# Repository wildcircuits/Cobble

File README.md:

# Cobble 

Cobble is a development board designed to give easy access to sound, environment, and input while being easy to program with CircuitPython.

## Features

- ESP32-S3 Supermini module
- Vibration Sensor
- Light Sensor
- RGB LED
- Speaker
- Button
- Grove Connector
- Stemma Connector
- Battery Connector
- Power Switch 
- IO Header

## Board revisions

| Revision | Status | Notes |
| --- | --- | --- |
| **Rev 2** | **Current - first production run** | Fixed the Stemma connector, which was wired backwards on Rev 1 (the main change). Silkscreen updated, including a QR code. R3 (light sensor divider resistor) set to 10k - it worked at 1M as well, but 10k matches the other 10k resistor and reduces unique part count. Gerbers are in `Cobble-board/fab`. |
| **Rev 1** | Design Validation | 2 layer board test with all features implemented.  Fabricated 3 boards at OSHPark. Established the current pin map (below). |
| **Rev 0** | Concept Validation | Single-layer test board with seperate schematic and layout in `Cobble-board-test/` |

Pins did not change between Rev 1 and Rev 2, so the pin map below applies to both.

## ESP32S3-supermini Pinout

Link: https://www.espboards.dev/esp32/esp32-s3-super-mini/

## Pin mapping 

| ESP32-S3-super-mini Pin | Function | Notes | CircuitPython |
| --- | --- | --- | --- |
| GPIO7 | Light Sensor | Analog read with `analogio.AnalogIn`. GPIO7 is analog-capable, so it maps to A6. | `board.A6` |
| GPIO35 | PushButton | Configure as input with pull up. PushButton is active low. | `board.IO35` |
| GPIO9 | Vibration Sensor | Configure as input with pull up. Vibration is active low. | `board.IO9` |
| GPIO8 | Buzzer | **Never leave high!** Set as output low when not in use. Drive with PWM 50% duty cycle to create sound. | `board.IO8` |
| GPIO48 | NeoPixel | RGB status LED. | `board.IO48` |
| GPIO16 | SCL | I2C for the J3 Stemma and J4 Grove connectors. 4k7 pull-up pads on the board (R4-R7) are do-not-place, so pull-ups come from the attached device. | `board.IO16` |
| GPIO17 | SDA | I2C for the J3 Stemma and J4 Grove connectors. 4k7 pull-up pads on the board (R4-R7) are do-not-place, so pull-ups come from the attached device. | `board.IO17` |
| GPIO1, GPIO2, GPIO4, GPIO5, GPIO6, GPIO15 | Header GPIOs | General-purpose header pins aligned with power and ground pairs. | `board.IOx` |
| GPIO10, GPIO11, GPIO12, GPIO13 | Header GPIOs (SPI) | Header pins aligned for SPI (native SPI pins). | `board.IOx` |

Reference example code using the full Rev 1 pin map: `CircuitPython/Cobble-Rev1/test/code.py`.

## Design notes

Note about 5V Power:
- When USB is connected this will be 5V from VBUS
- When running from a battery this will be Vbatt-V_protection_diode
- Battery can only charge when USB is connected and power switch is 'ON'

## CircuitPython Notes

Testing completed with: 
- Version: 10.3.1
- Using the ESP32-S3-Zero build of CircuitPython.  It is a good standin for the super mini on our board: https://circuitpython.org/board/waveshare_esp32_s3_zero/
- the `boot_out.txt` file is an informational text file automatically generated on the root of the CIRCUITPY drive every time a CircuitPython board powers up or resets.  Contains:
  - CircuitPython Version
  - Build Date
  - Board Model
  - Board ID
  - UID
  - MAC

### Tips & tricks
- **Pin objects**: 
  - Digital pins are `board.IOx` (e.g. `board.IO35` for the pushbutton)
  - The analog light sensor is `board.A6` (GPIO7).
- **Analog input**: 
  - Use `analogio.AnalogIn(pin)`. There is no `board.ADC()`.
  - Read the value with `.value` (0–65535)
- **Digital input**: 
  - set direction with `digitalio.Direction.INPUT`
  - button (GPIO35) and vibration sensor (GPIO9) use `digitalio.Pull.UP` and read active low
- **Digital input Pull UP / DOWN**: 
  - set a pull up with `.pull = digitalio.Pull.UP`
  - set a pull down with `.pull = digitalio.Pull.DOWN`
- **I2C**: 
  - Use `busio.I2C(scl_pin, sda_pin)` (e.g. `busio.I2C(board.IO16, board.IO17)`)
  - The 4k7 pull-up pads (R4-R7) are do-not-place, so the bus may not initialize or get ACKs
    until an attached device brings its own pull-ups.  Wrap I2C calls and re-scan in a loop so
    a device plugged in mid-run is picked up without crashing.  You can install your own 4k7 resistors (0603 or leaded, not both) if desired.
  - `scan()` only works while the bus is held with `try_lock()`
  - GPIO16/17 are IOMUX-capable on the ESP32-S3, so `busio.I2C` is allowed on them.
  - The REPL console is on USB, so GPIO16/17 are free for I2C.
- **NeoPixel**: the constructor is `neopixel.NeoPixel(pin, n, brightness=...)` —
  the `pixel_bit_depth` keyword is not accepted on this build.

### Example Code Snippets
#### **I2C**: Configure I2C bus and scan for devices
``` python
import board
import busio

i2c = busio.I2C(board.IO16, board.IO17)  # SCL, SDA for J3/J4 connectors

def scan_i2c():
    """Scan the I2C bus and return list of connected device addresses."""
    devices = []
    if not i2c.try_lock():
        return devices
    try:
        for addr in range(0x08, 0x78):
            try:
                i2c.writeto(addr, b"")
                devices.append(addr)
            except OSError:
                pass
    finally:
        i2c.unlock()
    return devices
```

#### **Light Sensor**: Read the analog value (GPIO7 / A6)
``` python
import board
import analogio

light = analogio.AnalogIn(board.A6)
print(light.value)  # 0-65535
```

#### **PushButton**: Input with pull up, active low (GPIO35)
``` python
import board
import digitalio

button = digitalio.DigitalInOut(board.IO35)
button.direction = digitalio.Direction.INPUT
button.pull = digitalio.Pull.UP

pressed = not button.value  # True when the button is pressed
```

#### **Speaker**: Configure pin for PWM and play tone
``` python
import board
import pwmio
import time

piezo = pwmio.PWMOut(board.IO8, frequency=440, duty_cycle=0, variable_frequency=True)

# 8 notes of a C Major octave (C5 to C6) in Hertz
OCTAVE_NOTES = [
    523,  # C5
    587,  # D5
    659,  # E5
    698,  # F5
    784,  # G5
    880,  # A5
    988,  # B5
]

def startup_song():
    # Loop through each note in the octave scale
    for freq in OCTAVE_NOTES:
        piezo.frequency = freq
        piezo.duty_cycle = 32768  # Start tone (50% duty cycle)
        time.sleep(0.1)           # Play note for 0.1s
    
    # Mute tone and clean up hardware resource
    piezo.duty_cycle = 0
```

#### **RGB LED Neopixel**: Configure pin and show RGB colors
``` python
import board
import neopixel

# Initialize NeoPixel on the default board pin (or replace board.NEOPIXEL with board.IOx)
pixel = neopixel.NeoPixel(board.IO48, 1, brightness=0.2)

# Set color to Green (RGB: Red=0, Green=255, Blue=0)
pixel[0] = (0, 255, 0)

def wheel(pos):
    """Return an RGB tuple for a position 0-255 around the color wheel."""
    pos %= 256
    if pos < 85:
        return (255 - pos * 3, pos * 3, 0)
    elif pos < 170:
        pos -= 85
        return (0, 255 - pos * 3, pos * 3)
    else:
        pos -= 170
        return (pos * 3, 0, 255 - pos * 3)

# Rainbow fade state: hue position (0-255) and per-step increment
hue = 0
HUE_STEP = 2  # higher = faster cycle

def rainbow():
    """Advance the hue and set the pixel to the new rainbow color."""
    global hue
    hue = (hue + HUE_STEP) % 256
    pixel[0] = wheel(hue)
```

#### Included modules for CircuitPython 10.3.1:
_asyncio
_bleio
_bleio (native)
_eve
_pixelmap
adafruit_bus_device
adafruit_pixelbuf
aesio
alarm
analogbufio
analogio
array
atexit
audiobusio
audiocore
audioi2sin
audiomixer
audiomp3
binascii
bitbangio
bitmapfilter
bitmaptools
board
builtins
builtins.pow3
busdisplay
busio
busio.SPI
busio.UART
canio
codeop
collections
countio
digitalio
displayio
epaperdisplay
errno
espcamera
espidf
espnow
espulp
fontio
fourwire
framebufferio
frequencyio
getpass
gifio
hashlib
i2cdisplaybus
io
ipaddress
jpegio
json
keypad
keypad.KeyMatrix
keypad.Keys
keypad.ShiftRegisterKeys
keypad_demux
keypad_demux.DemuxKeyMatrix
locale
lvfontio
math
max3421e
mdns
memorymap
microcontroller
msgpack
neopixel_write
neopixel
nvm
onewireio
os
os.getenv
paralleldisplaybus
ps2io
pulseio
pwmio
qrio
rainbowio
random
re
rgbmatrix
rotaryio
rtc
sdcardio
sdioio
select
sharpdisplay
socketpool
socketpool.socketpool.AF_INET6
ssl
storage
struct
supervisor
supervisor.get_setting
synthio
sys
terminalio
tilepalettemapper
time
touchio
traceback
ulab
usb
usb_audio
usb_cdc
usb_hid
usb_midi
vectorio
warnings
watchdog
wifi
zlib

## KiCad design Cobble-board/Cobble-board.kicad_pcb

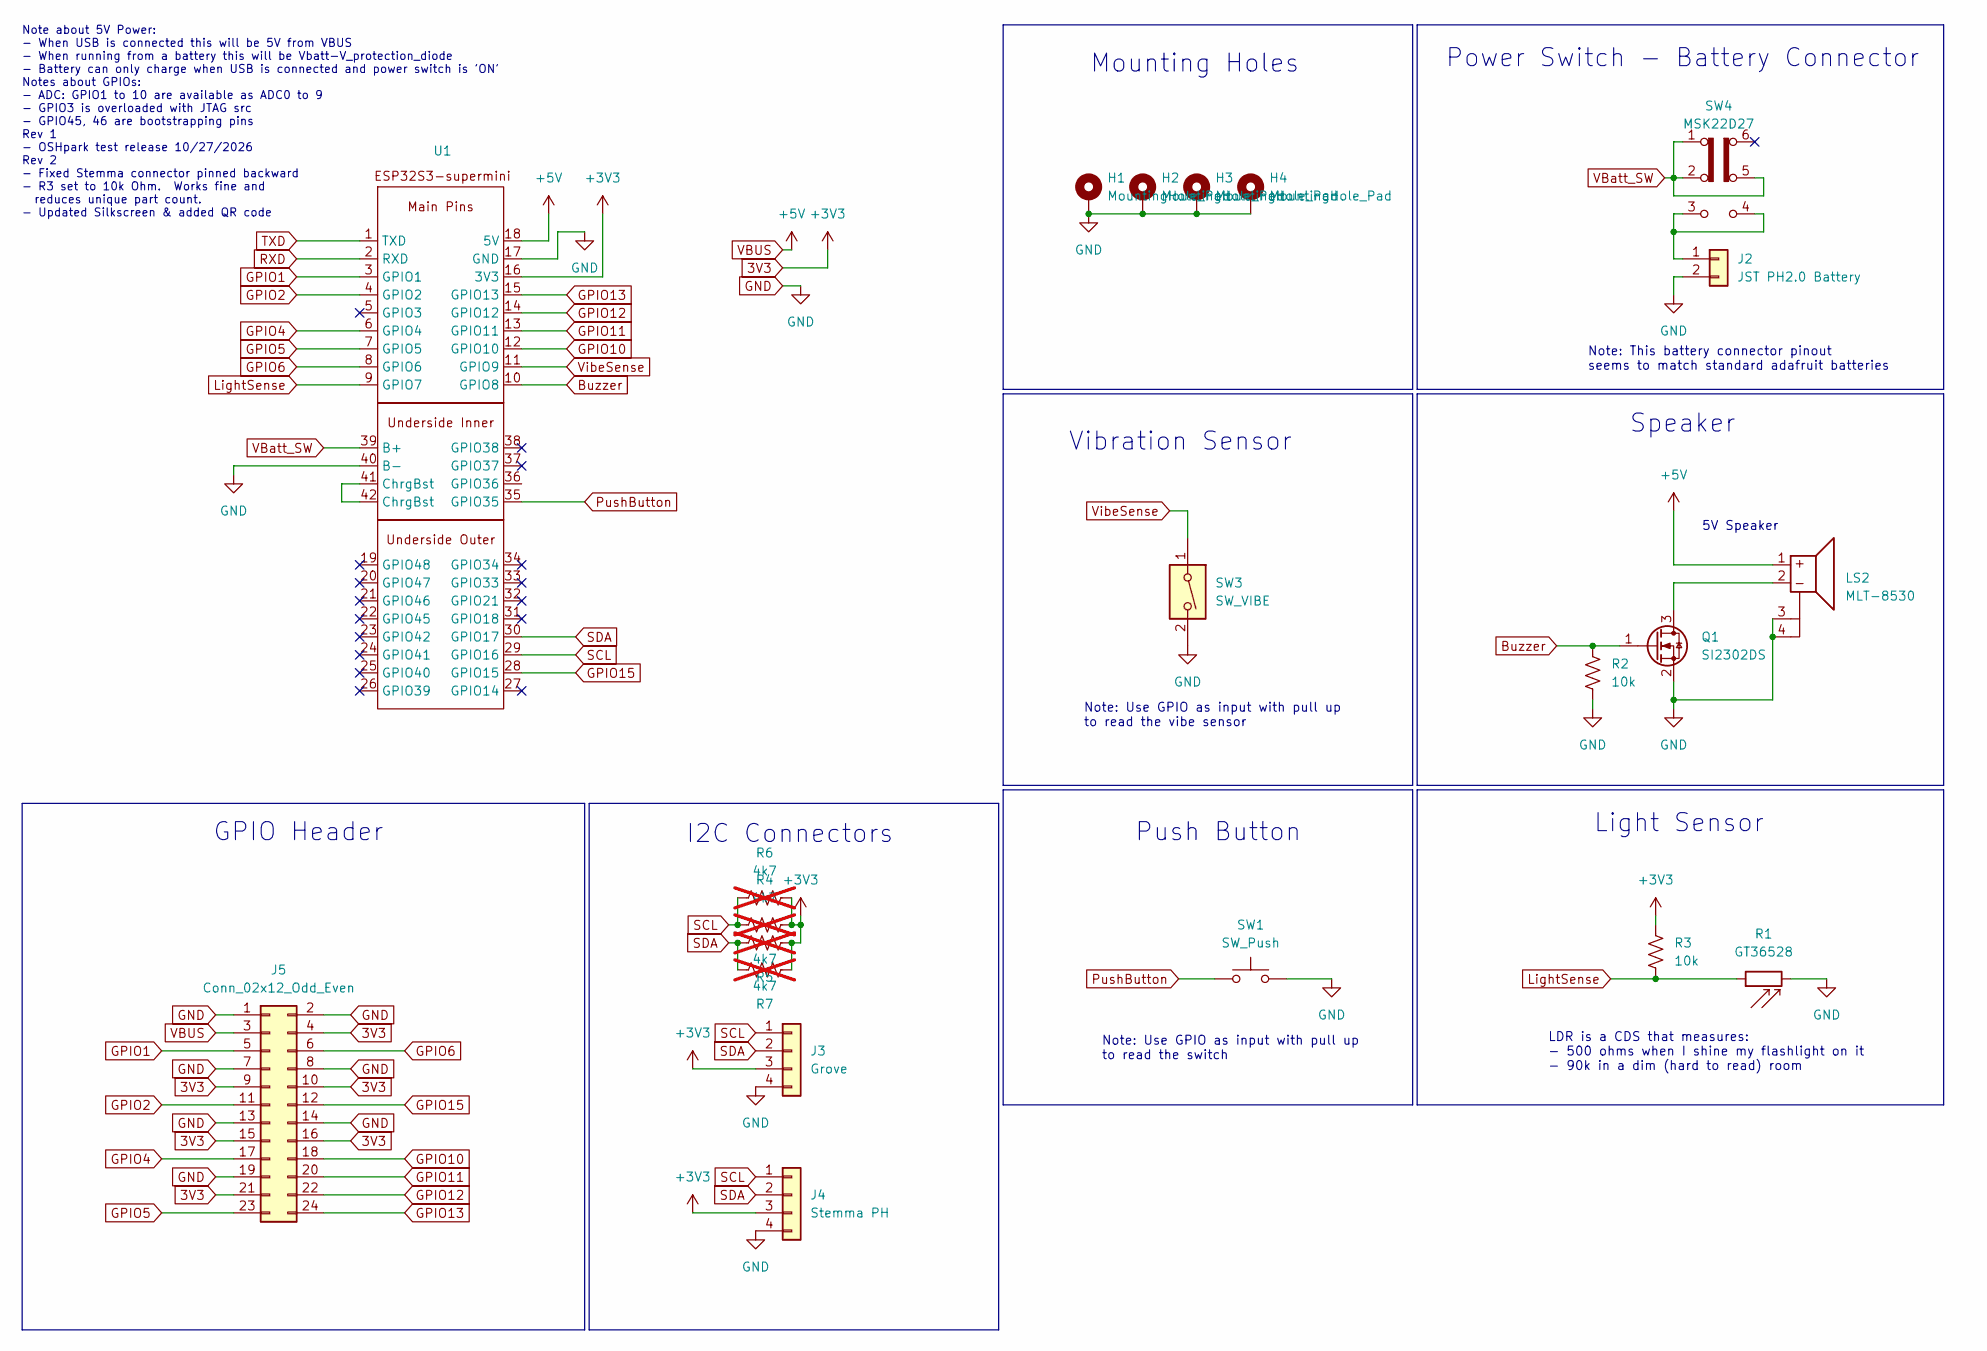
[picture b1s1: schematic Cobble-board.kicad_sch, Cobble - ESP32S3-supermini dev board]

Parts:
H1, H2, H3, H4: MountingHole_Pad; MountingHole_3.2mm_M3_Pad_TopBottom
J2: JST PH2.0 Battery; JST_PH_B2B-PH-SM4-TB_1x02-1MP_P2.00mm_Vertical
J3: Grove; JST_PH_B4B-PH-SM4-TB_1x04-1MP_P2.00mm_Vertical
J4: Stemma PH; GROVE-HW4-SMD-2.0
J5: Conn_02x12_Odd_Even; PinHeader_2x12_P2.54mm_Vertical_SMD
LS2: MLT-8530
Q1: SI2302DS; SOT-23_Handsoldering
R1: GT36528
R2, R3: 10k; R_0603_1608Metric_Pad0.98x0.95mm_HandSolder
R4, R5: 4k7; R_0603_1608Metric_Pad0.98x0.95mm_HandSolder; not fitted
R6, R7: 4k7; R_Axial_DIN0204_L3.6mm_D1.6mm_P5.08mm_Horizontal; not fitted
SW1: SW_Push; SW_Push_1P1T
SW3: SW_VIBE; X160
SW4: MSK22D27
U1: ESP32S3-supermini-v2

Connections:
3V3: J3.3, J4.3, J5.4, J5.9, J5.10, J5.15, J5.16, J5.21, R3.1, R4.2, R5.2, R6.2, R7.2, U1.16 (3V3)
Buzzer: Q1.1 (G), R2.1, U1.10 (GPIO8)
GND: H1.1 (1_1), H2.1 (1_1), H3.1 (1_1), H4.1 (1_1), J2.2, J2.MP, J3.4, J3.MP, J4.4, J4.5, J4.6, J5.1, J5.2, J5.7, J5.8, J5.13, J5.14, J5.19, LS2.3 (Dummy), LS2.4 (Dummy), Q1.2 (S), R1.2, R2.2, SW1.2, SW3.2, U1.17 (GND), U1.40 (B-)
GPIO1: J5.5, U1.3 (GPIO1)
GPIO2: J5.11, U1.4 (GPIO2)
GPIO4: J5.17, U1.6 (GPIO4)
GPIO5: J5.23, U1.7 (GPIO5)
GPIO6: J5.6, U1.8 (GPIO6)
GPIO10: J5.18, U1.12 (GPIO10)
GPIO11: J5.20, U1.13 (GPIO11)
GPIO12: J5.22, U1.14 (GPIO12)
GPIO13: J5.24, U1.15 (GPIO13)
GPIO15: J5.12, U1.28 (GPIO15)
LightSense: R1.1, R3.2, U1.9 (GPIO7)
unnamed: J2.1, SW4.3 (C), SW4.4 (A)
unnamed: LS2.2, Q1.3 (D)
PushButton: SW1.1, U1.35 (GPIO35)
RXD: U1.2 (RXD)
SCL: J3.1, J4.1, R4.1, R6.1, U1.29 (GPIO16)
SDA: J3.2, J4.2, R5.1, R7.1, U1.30 (GPIO17)
TXD: U1.1 (TXD)
VBUS: J5.3, LS2.1, U1.18 (5V)
VBatt_SW: SW4.1 (A), SW4.2 (B), SW4.5 (B), U1.39 (B+)
VibeSense: SW3.1, U1.11 (GPIO9)

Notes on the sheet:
Note: Use GPIO as input with pull up to read the switch
Note: This battery connector pinout seems to match standard adafruit batteries
5V Speaker
LDR is a CDS that measures: - 500 ohms when I shine my flashlight on it - 90k in a dim (hard to read) room
Mounting Holes
I2C Connectors
Vibration Sensor
Speaker
Note: Use GPIO as input with pull up to read the vibe sensor
Note about 5V Power: - When USB is connected this will be 5V from VBUS - When running from a battery this will be Vbatt-V_protection_diode - Battery can only charge when USB is connected and power switch is 'ON' Notes about GPIOs: - ADC: GPIO1 to 10 are available as ADC0 to 9 - GPIO3 is overloaded 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
Push Button
GPIO Header
Light Sensor
Power Switch - Battery Connector

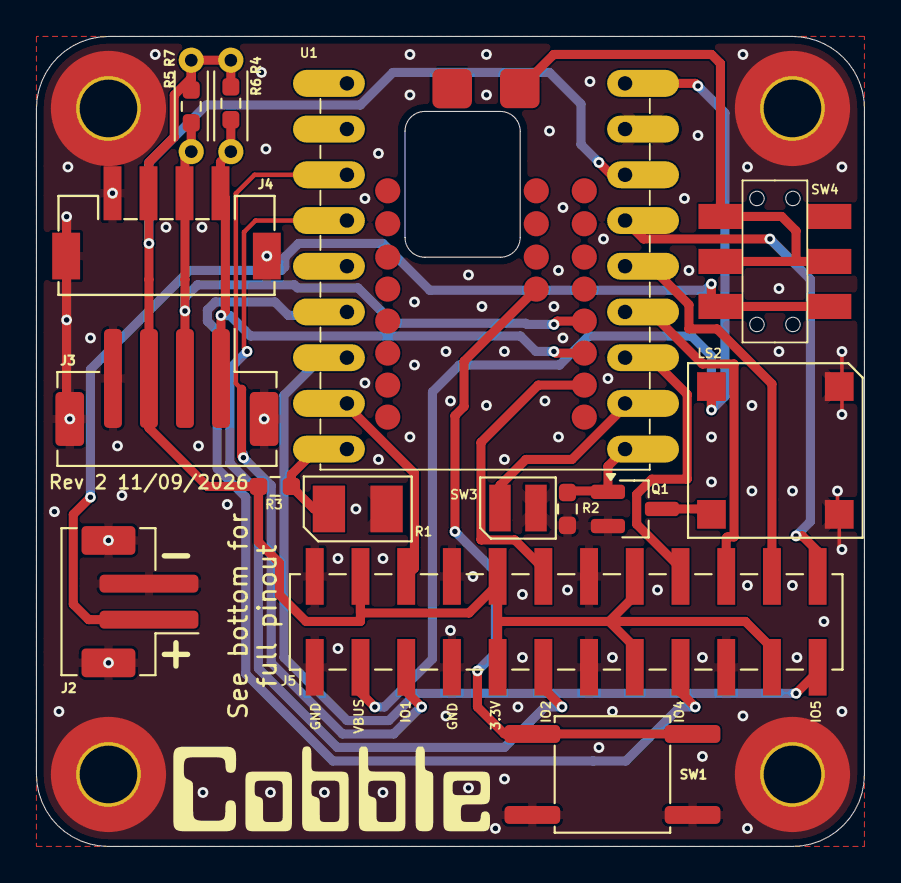
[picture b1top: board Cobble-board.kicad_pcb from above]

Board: 2 copper layers, 46.0 x 45.0 mm, 21 parts (0 on the bottom side), 22 nets.

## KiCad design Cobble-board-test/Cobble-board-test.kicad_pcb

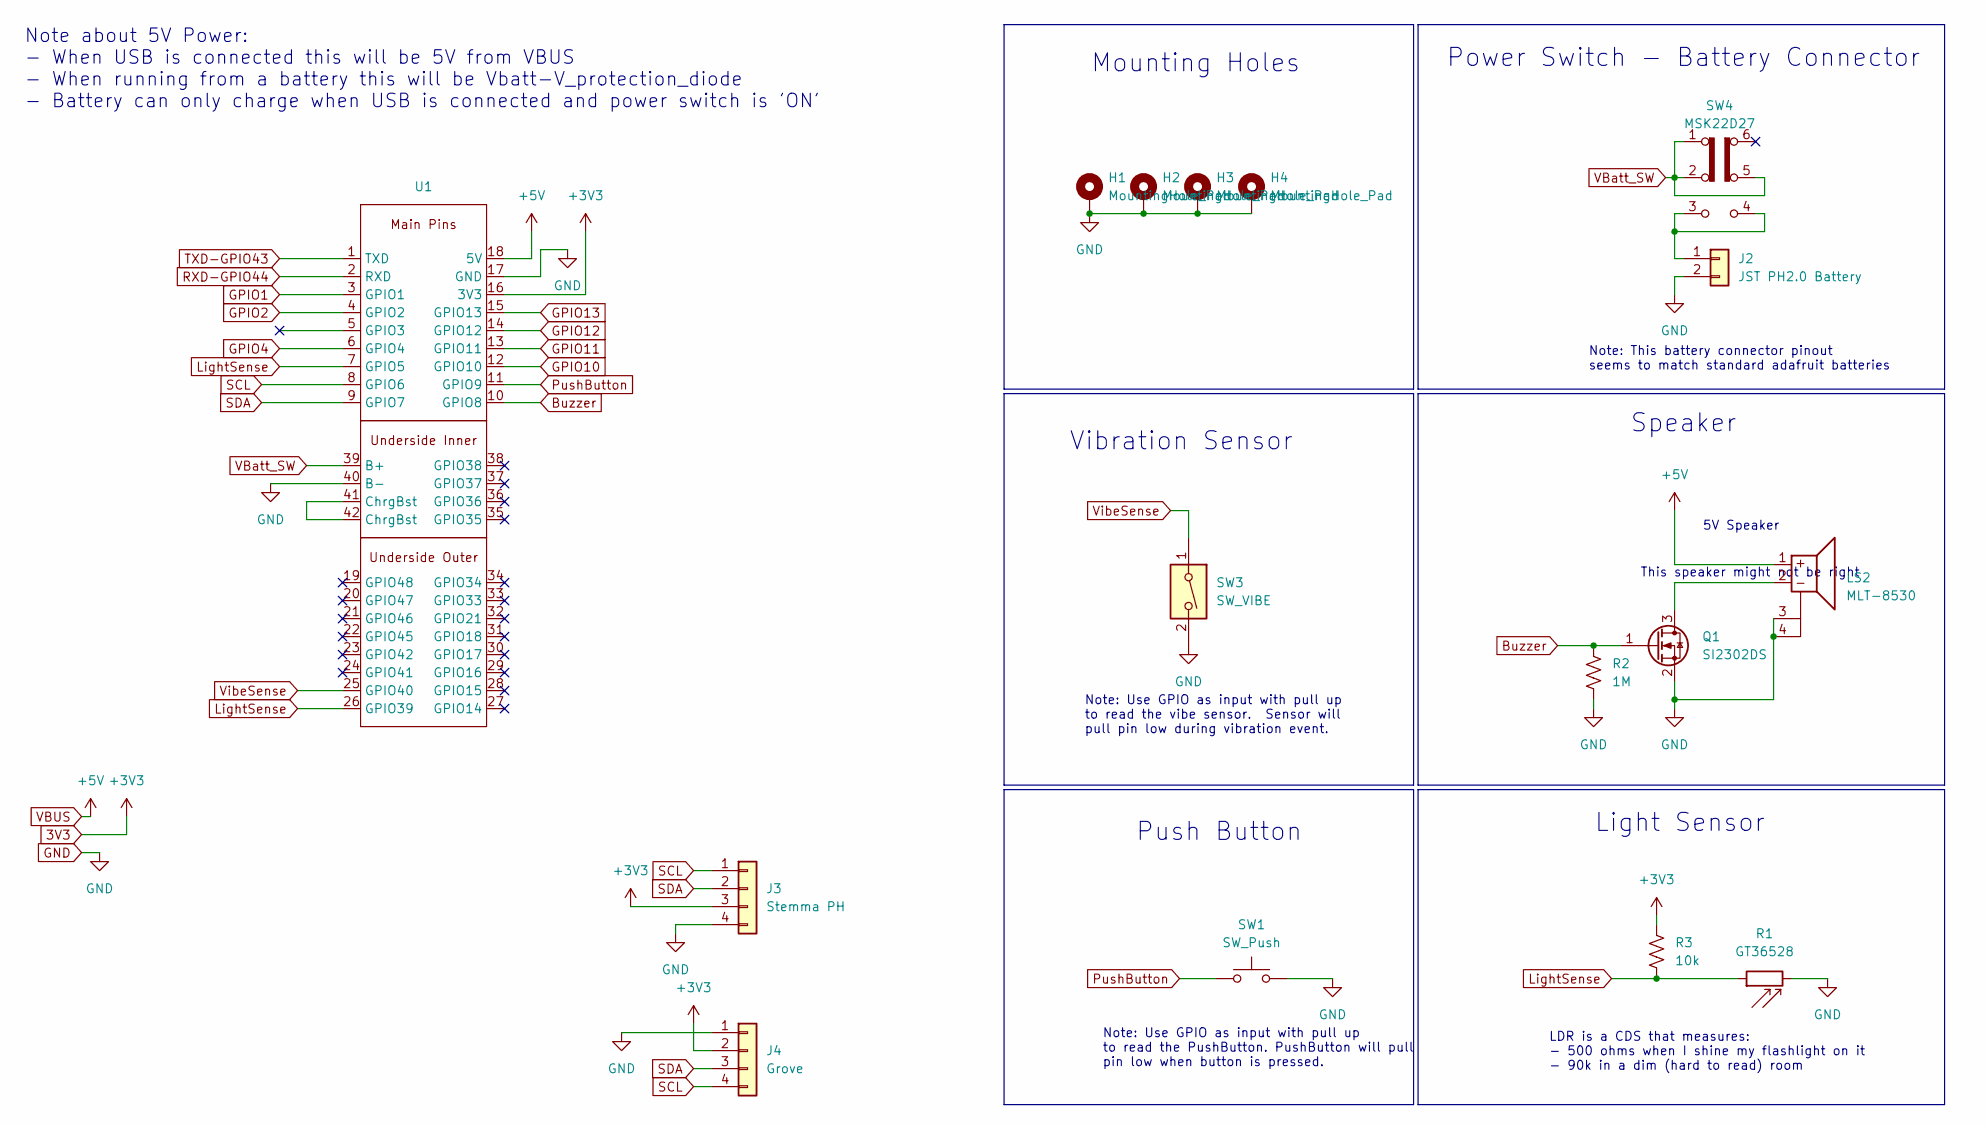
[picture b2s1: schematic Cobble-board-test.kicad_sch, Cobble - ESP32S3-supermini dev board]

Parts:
H1, H2, H3, H4: MountingHole_Pad; MountingHole_3.2mm_M3_Pad_TopBottom
J2: JST PH2.0 Battery; Battery_1x02_P2.00mm_Horizontal
J3: Stemma PH; Stemma_Grove_1x04_P2.00mm_Horizontal
J4: Grove; Stemma_Grove_1x04_P2.00mm_Horizontal
LS2: MLT-8530
Q1: SI2302DS; SOT-23_Handsoldering
R1: GT36528
R2: 1M; R_0603_1608Metric_Pad0.98x0.95mm_HandSolder
R3: 10k; R_0603_1608Metric_Pad0.98x0.95mm_HandSolder
SW1: SW_Push; SW_Push_1P1T_NO_CK_KSC6xxG
SW3: SW_VIBE; X160
SW4: MSK22D27
U1: ESP32S3-supermini

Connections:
3V3: J3.3, J4.2, R3.1, U1.16 (3V3)
Buzzer: Q1.1 (G), R2.1, U1.10 (GPIO8)
GND: H1.1 (1_1), H2.1 (1_1), H3.1 (1_1), H4.1 (1_1), J2.2, J3.4, J4.1, LS2.3 (Dummy), LS2.4 (Dummy), Q1.2 (S), R1.2, R2.2, SW1.2, SW3.2, U1.17 (GND), U1.40 (B-)
GPIO1: U1.3 (GPIO1)
GPIO2: U1.4 (GPIO2)
GPIO4: U1.6 (GPIO4)
GPIO10: U1.12 (GPIO10)
GPIO11: U1.13 (GPIO11)
GPIO12: U1.14 (GPIO12)
GPIO13: U1.15 (GPIO13)
unnamed: J2.1, SW4.3 (C), SW4.4 (A)
unnamed: LS2.2, Q1.3 (D)
unnamed: U1.41 (ChrgBst), U1.42 (ChrgBst)
PushButton: SW1.1, U1.11 (GPIO9)
RXD-GPIO44: U1.2 (RXD)
SCL: J3.1, J4.4, U1.8 (GPIO6)
SDA: J3.2, J4.3, U1.9 (GPIO7)
TXD-GPIO43: U1.1 (TXD)
VBUS: LS2.1, U1.18 (5V)
VBatt_SW: SW4.1 (A), SW4.2 (B), SW4.5 (B), U1.39 (B+)
VibeSense: SW3.1, U1.25 (GPIO40)

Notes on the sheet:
This speaker might not be right
Note: Use GPIO as input with pull up to read the PushButton. PushButton will pull pin low when button is pressed.
Note: This battery connector pinout seems to match standard adafruit batteries
5V Speaker
LDR is a CDS that measures: - 500 ohms when I shine my flashlight on it - 90k in a dim (hard to read) room
Mounting Holes
Vibration Sensor
Speaker
Note: Use GPIO as input with pull up to read the vibe sensor. Sensor will pull pin low during vibration event.
Note about 5V Power: - When USB is connected this will be 5V from VBUS - When running from a battery this will be Vbatt-V_protection_diode - Battery can only charge when USB is connected and power switch is 'ON'
Push Button
Light Sensor
Power Switch - Battery Connector

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
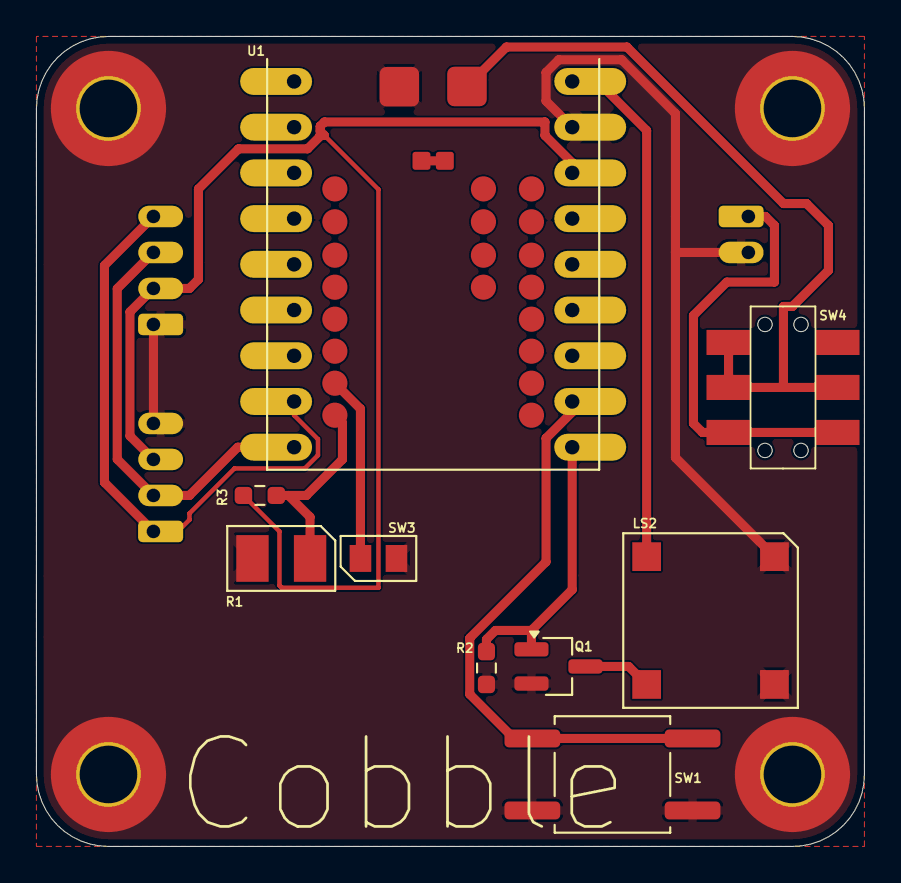
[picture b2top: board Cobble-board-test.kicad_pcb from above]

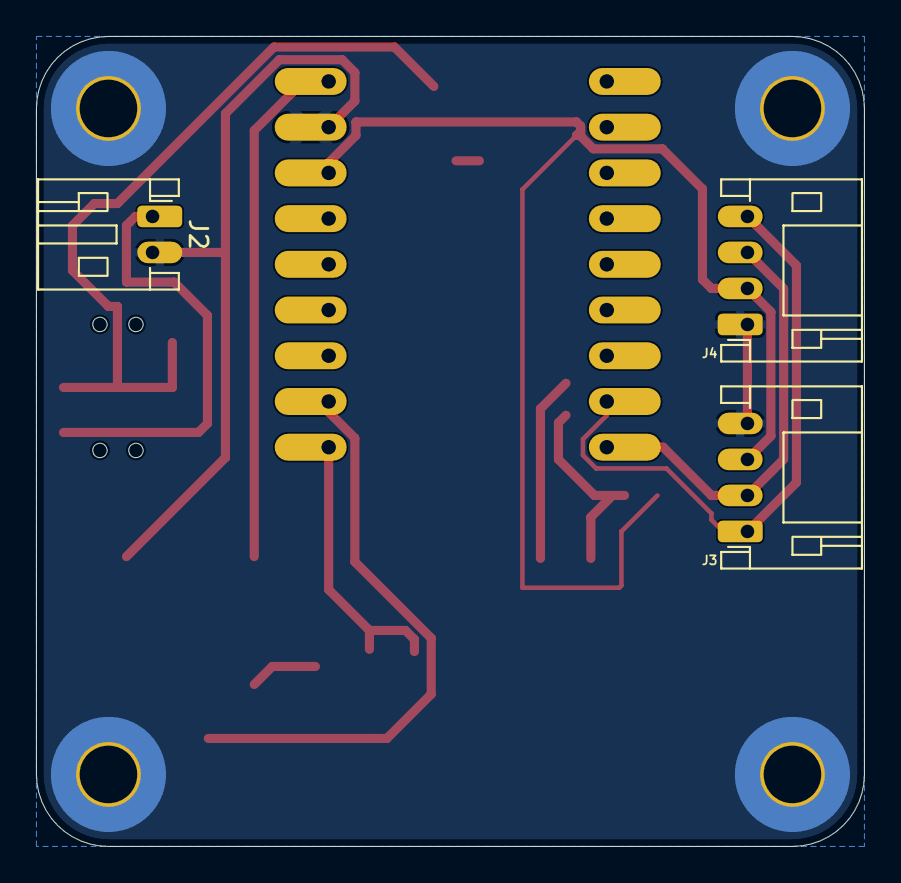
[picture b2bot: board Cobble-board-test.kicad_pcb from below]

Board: 2 copper layers, 46.0 x 45.0 mm, 16 parts (3 on the bottom side), 13 nets.

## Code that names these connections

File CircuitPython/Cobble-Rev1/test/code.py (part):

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
Rev 1 pin map
-------------
  - Buzzer (GPIO8 / board.IO8)   - PWM beep, 50% duty, never left high
  - Push button (GPIO35 / board.IO35) - active-low, pull-up
  - NeoPixel (GPIO48 / board.IO48) - RGB LED
  - Light sensor (GPIO7 / board.A6) - analog read
  - Vibration sensor (GPIO9 / board.IO9) - active-low, pull-up
  - I2C: SDA (GPIO17 / board.IO17), SCL (GPIO16 / board.IO16)
      NOTE: the board has no I2C pull-ups, so bus init / scan can fail until an
      I2C device is attached.  That is expected, so every I2C call is wrapped and
      the scan is repeated in the monitor loop - a device plugged in while the
      code runs is picked up on the next pass, and one unplugged mid-run is
      handled without crashing.  REPL console is on USB, so GPIO16/17 are free.
      busio.I2C.scan() only works while the bus is held with try_lock().
  - Header GPIO pins aligned with power and ground:
    - GPIO1, GPIO2, GPIO4, GPIO5, GPIO6, GPIO15
      GPIO1 drives the test servo (PWM output).
      GPIO2, GPIO4, GPIO5, GPIO6, GPIO15 are inputs with pull-downs.
  - Header GPIO pins aligned for SPI:
    - GPIO10, GPIO11, GPIO12, GPIO13 - inputs with pull-downs.
      Pull any header input high by hand and the monitor loop reports it.

Extra checks carried over from the Rev 1 example code
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import busio

# -- Rev 1 pin map ---------------------------------------------------------------
BUZZER_PIN = board.IO8      # GPIO8
BUTTON_PIN = board.IO35     # GPIO35
NEOPIXEL_PIN = board.IO48   # GPIO48
LIGHT_PIN = board.A6        # GPIO7
VIBRATION_PIN = board.IO9   # GPIO9
SERVO_PIN = board.IO1       # GPIO1 - expected test servo
SDA_PIN = board.IO17        # GPIO17
SCL_PIN = board.IO16        # GPIO16

# Servo timing: 20 ms frame, 0.5-2.5 ms pulse -> 50 Hz PWM
SERVO_FREQ_HZ = 50
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        return None


# -- Buzzer (GPIO8) --------------------------------------------------------------
# GPIO8: PWM 50% duty cycle produces sound. NEVER leave high!
# Mutable container so beep() can reassign without `global`.
_buzzer = {"pwm": None}

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def buzzer_open(freq):
    """Create the buzzer PWM output at freq, or return None if it cannot be opened."""
    _buzzer["pwm"] = safe("buzzer", lambda: manage(
        pwmio.PWMOut(BUZZER_PIN, frequency=int(freq), duty_cycle=0,
                     variable_frequency=True)))
    return _buzzer["pwm"]

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    return safe(label, build)


button = make_input(BUTTON_PIN, "button (GPIO35)", digitalio.Pull.UP)


def button_pressed():
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    set_pixel(*wheel(hue))


# -- Light sensor (GPIO7 / A6, analog) -------------------------------------------
light_sensor = safe("light sensor (GPIO7 / A6)",
                    lambda: manage(analogio.AnalogIn(LIGHT_PIN)))


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        return None


# -- Vibration sensor (GPIO9, active low, pull-up) -------------------------------
# Detected with a hardware falling-edge pulse counter so a short shake that happens
# between polls is still counted.  If countio cannot claim the pin, fall back to
# reading the pin level.
vibration_counter = safe("vibration counter (GPIO9)", lambda: manage(
    countio.Counter(VIBRATION_PIN, edge=countio.Edge.FALL, pull=digitalio.Pull.UP)))
vibration = None
if vibration_counter is None:
    vibration = make_input(VIBRATION_PIN, "vibration sensor (GPIO9)", digitalio.Pull.UP)


def vibration_pulses():
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        return False


# -- Servo (GPIO1) ---------------------------------------------------------------
def servo_duty(ms):
    """Convert a servo pulse width in ms to a 16-bit duty cycle."""
    return int((ms / SERVO_PERIOD_MS) * 65535)
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    return True


# -- I2C (SDA GPIO17, SCL GPIO16) ------------------------------------------------
# scan() and every read/write need the bus held with try_lock(), so the scan
# happens inside a try_lock()/unlock() pair.
_i2c = {"bus": None}
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    """Open the I2C bus, or return None if it cannot be opened (no pull-ups)."""
    if _i2c["bus"] is None:
        def build():
            # busio.I2C takes SCL first, then SDA.  GPIO16/17 are IOMUX-capable
            # on the ESP32-S3, so busio is allowed on them.
            return manage(busio.I2C(SCL_PIN, SDA_PIN, frequency=100000))

        _i2c["bus"] = safe("I2C bus", build)
        if _i2c["bus"] is not None and report:
            print("    I2C bus open: SCL=GPIO16, SDA=GPIO17")
    return _i2c["bus"]


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print("=== Cobble Board Smoke Test (Rev 1) ===\n")

# 1. Buzzer test - startup song, then three short beeps
print("[1] Buzzer test (GPIO8): startup song, then 3 beeps at 440 Hz")
startup_song()
for _ in range(3):
    beep(440, 0.15)
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set_pixel(0, 0, 0)  # off
print("    NeoPixel OK\n")

# 3. Light sensor test (GPIO7 / A6) - sample, cover the sensor and compare
print("[3] Light sensor test (GPIO7 / A6)")
samples = []
for _ in range(3):
    samples.append(read_light())
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else:
    print("    Light sensor not readable\n")

# 4. Vibration sensor test (GPIO9) - shake the board, expect a beep
print("[4] Vibration sensor test (GPIO9)")
if vibration_counter is not None:
    print(f"    reading via the hardware pulse counter (countio)")
else:
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clear_vibration()  # the beep itself shakes the board, so drop those pulses
print("    Vibration sensor OK\n")

# 5. Button test - wait for press (GPIO35, active low)
print(f"[5] Button test (GPIO35): press the button ({BUTTON_TIMEOUT} s timeout)")
set_pixel(0, 0, 255)  # blue while waiting
start = time.monotonic()
pressed = False
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time.sleep(0.5)
set_pixel(0, 0, 0)

# 6. Servo test - expect a servo on GPIO1
print(f"[6] Servo test (GPIO1): {int(SERVO_FREQ_HZ)} Hz frame, sweep "
      f"{SERVO_MIN_MS} -> {SERVO_MAX_MS} ms")
servo = safe("servo (GPIO1)",
             lambda: manage(pwmio.PWMOut(SERVO_PIN, frequency=SERVO_FREQ_HZ, duty_cycle=0)))
if servo is not None:
    for ms in (SERVO_MIN_MS, 1.0, 1.5, 2.0, SERVO_MAX_MS, 1.5):
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    print("    Servo sweep done (no movement is normal if no servo is attached)\n")

# 7. I2C scan - a device may already be attached, or appear later
print("[7] I2C scan (SDA GPIO17, SCL GPIO16)")
found = i2c_scan()
if found:
    print(f"    Found {len(found)} device(s): {describe(found)}")
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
